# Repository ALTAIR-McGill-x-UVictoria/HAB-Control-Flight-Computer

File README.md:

# HAB-Control-Flight-Computer
High Altitude Balloon Flight Computer

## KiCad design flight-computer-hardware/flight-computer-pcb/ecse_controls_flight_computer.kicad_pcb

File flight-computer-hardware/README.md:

# Hardware Information

Flight computer PCB designed on KiCad, a free PCB design software.

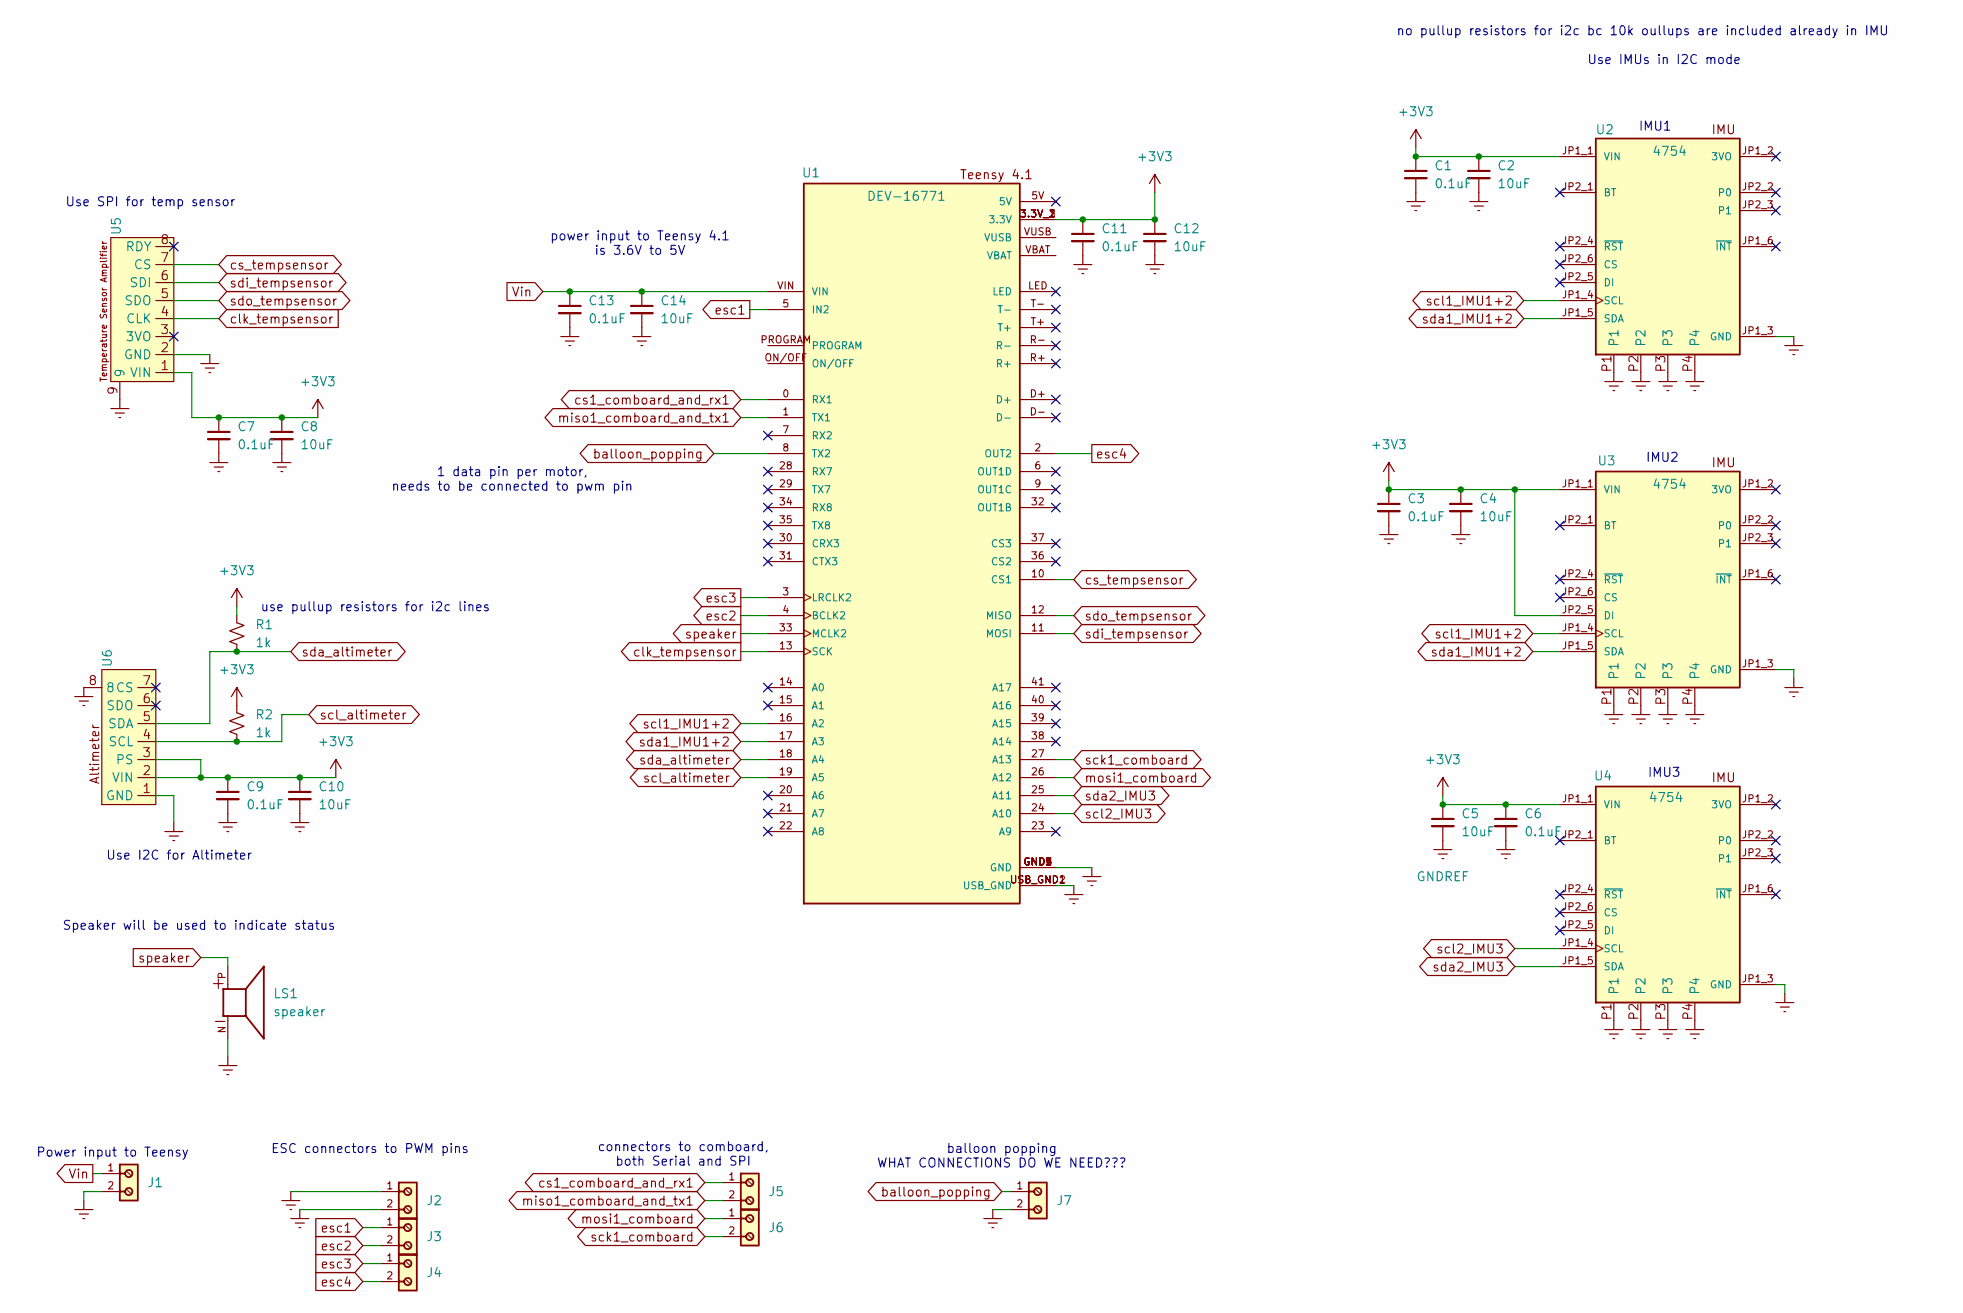
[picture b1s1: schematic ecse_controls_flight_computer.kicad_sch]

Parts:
C1, C3, C6, C7, C9, C11, C13: 0.1uF; C_0805_2012Metric_Pad1.18x1.45mm_HandSolder
C2, C4, C5, C8, C10, C12, C14: 10uF; C_0805_2012Metric_Pad1.18x1.45mm_HandSolder
J1, J2, J3, J4, J5, J6, J7: 691137710002; 691137710002-connector; PART-NUMBER 691137710002
LS1: speaker; PARTREV C
R1, R2: 1k; R_0805_2012Metric_Pad1.20x1.40mm_HandSolder
U1: DEV-16771; MODULE_DEV-16771; PARTREV 4.1
U2, U3, U4: 4754; MODULE_4754; PARTREV 2021-03-16
U5: temperature-amplifier
U6: altimeter

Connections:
+3V3: C1.1, C2.1, C3.1, C4.1, C5.1, C6.1, C7.1, C8.1, C9.1, C10.1, C11.1, C12.1, R1.1, R2.1, U1.3.3V_1 (3.3V), U1.3.3V_2 (3.3V), U1.3.3V_3 (3.3V), U2.JP1_1 (VIN), U3.JP1_1 (VIN), U3.JP2_5 (DI), U4.JP1_1 (VIN), U5.1 (VIN), U6.2 (VIN), U6.3 (PS)
GNDREF: C1.2, C2.2, C3.2, C4.2, C5.2, C6.2, C7.2, C8.2, C9.2, C10.2, C11.2, C12.2, C13.2, C14.2, J1.2, J2.1, J2.2, J7.2, LS1.N, U1.GND1 (GND), U1.GND2 (GND), U1.GND3 (GND), U1.GND4 (GND), U1.GND5 (GND), U1.USB_GND1 (USB_GND), U1.USB_GND2 (USB_GND), U2.JP1_3 (GND), U2.P1, U2.P2, U2.P3, U2.P4, U3.JP1_3 (GND), U3.P1, U3.P2, U3.P3, U3.P4, U4.JP1_3 (GND), U4.P1, U4.P2, U4.P3, U4.P4, U5.2 (GND), U5.9, U6.1 (GND), U6.8
Vin: C13.1, C14.1, J1.1, U1.VIN
balloon_popping: J7.1, U1.8 (TX2)
clk_tempsensor: U1.13 (SCK), U5.4 (CLK)
cs1_comboard_and_rx1: J5.1, U1.0 (RX1)
cs_tempsensor: U1.10 (CS1), U5.7 (CS)
esc1: J3.1, U1.5 (IN2)
esc2: J3.2, U1.4 (BCLK2)
esc3: J4.1, U1.3 (LRCLK2)
esc4: J4.2, U1.2 (OUT2)
miso1_comboard_and_tx1: J5.2, U1.1 (TX1)
mosi1_comboard: J6.1, U1.26 (A12)
sck1_comboard: J6.2, U1.27 (A13)
scl1_IMU1+2: U1.16 (A2), U2.JP1_4 (SCL), U3.JP1_4 (SCL)
scl2_IMU3: U1.24 (A10), U4.JP1_4 (SCL)
scl_altimeter: R2.2, U1.19 (A5), U6.4 (SCL)
sda1_IMU1+2: U1.17 (A3), U2.JP1_5 (SDA), U3.JP1_5 (SDA)
sda2_IMU3: U1.25 (A11), U4.JP1_5 (SDA)
sda_altimeter: R1.2, U1.18 (A4), U6.5 (SDA)
sdi_tempsensor: U1.11 (MOSI), U5.6 (SDI)
sdo_tempsensor: U1.12 (MISO), U5.5 (SDO)
speaker: LS1.P, U1.33 (MCLK2)

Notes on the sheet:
IMU3
use pullup resistors for i2c lines
IMU2
power input to Teensy 4.1 is 3.6V to 5V
Use I2C for Altimeter
connectors to comboard, both Serial and SPI
Use IMUs in I2C mode
balloon popping WHAT CONNECTIONS DO WE NEED???
Use SPI for temp sensor
no pullup resistors for i2c bc 10k oullups are included already in IMU
ESC connectors to PWM pins
1 data pin per motor, needs to be connected to pwm pin
Speaker will be used to indicate status
IMU1
Power input to Teensy

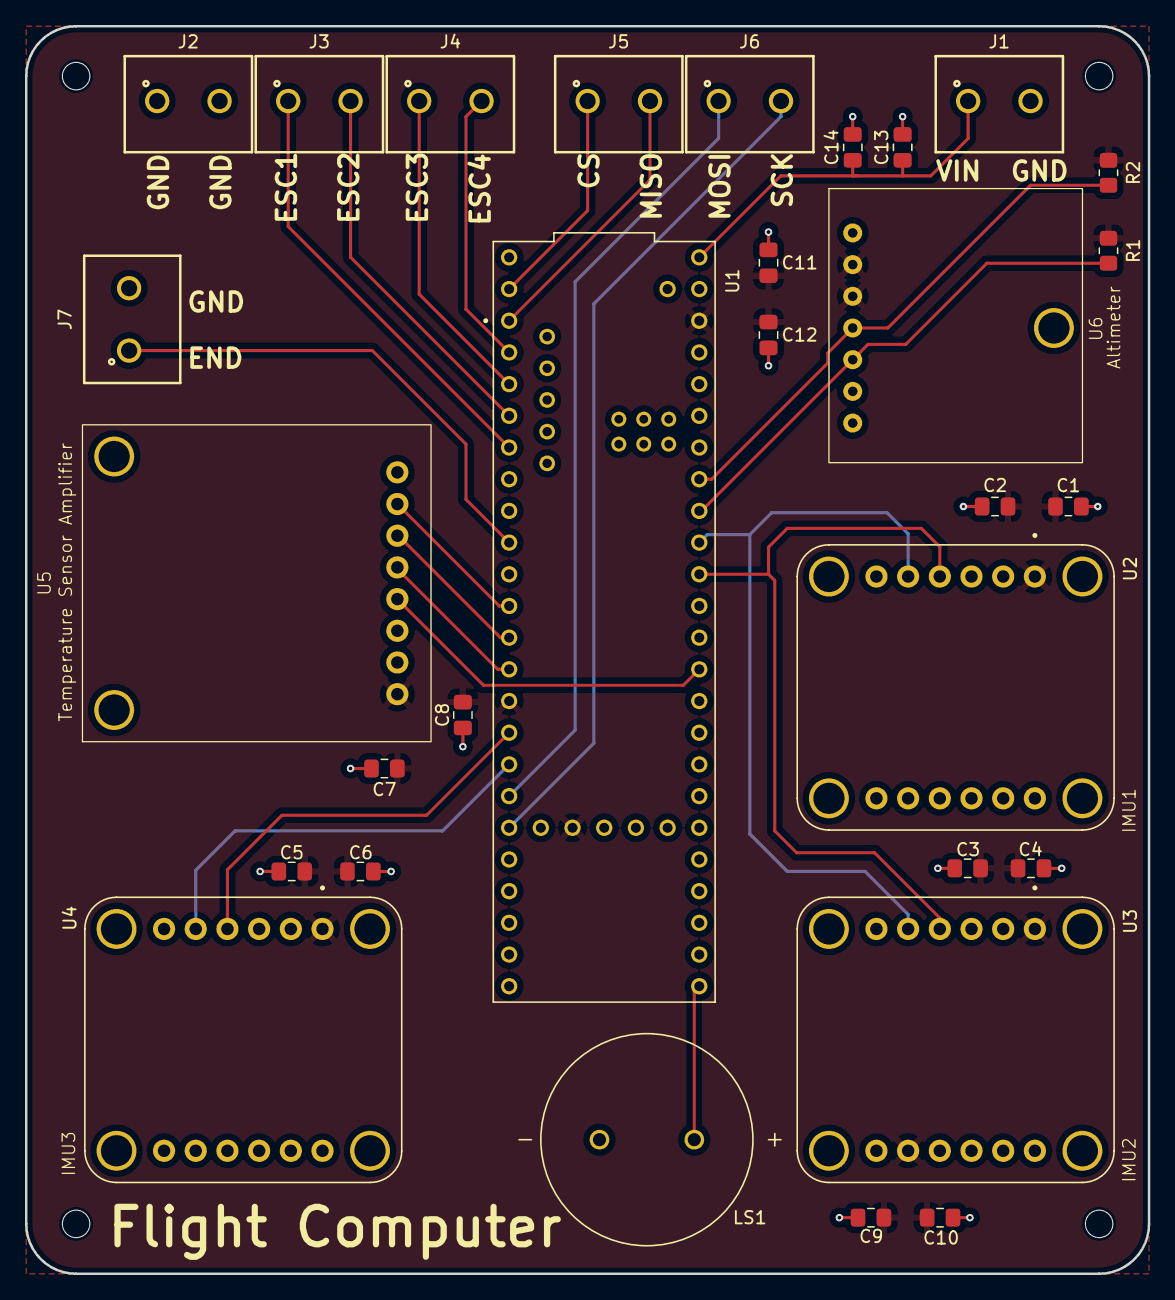
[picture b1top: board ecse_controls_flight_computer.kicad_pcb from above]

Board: 2 copper layers, 90.0 x 100.0 mm, 30 parts (0 on the bottom side), 23 nets.

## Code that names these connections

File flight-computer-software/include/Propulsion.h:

#ifndef PROPULSION_H
#define PROPULSION_H

#include <Arduino.h>
#include <Teensy_PWM.h>  // Include Teensy_PWM library
#include <TeensyThreads.h>

#define SPEAKER_PIN 33

class Propulsion {
public:
    // Constructor and destructor
    Propulsion(int esc1Pin = 4, int esc2Pin = 5)
        : ESC1_PIN(esc1Pin), ESC2_PIN(esc2Pin), esc1_pwm(nullptr), esc2_pwm(nullptr),
          leftThrottlePercent(0.0f), rightThrottlePercent(0.0f) {
        // Constructor initializes pin numbers, nulls the PWM pointers, and sets initial throttle to 0
    }
    
    ~Propulsion() {
        // Ensure resources are freed
        deinit();
    }
    
    // Main control methods
    bool init() {
        // Initialize Teensy_PWM objects with 0% duty cycle
        esc1_pwm = new Teensy_PWM(ESC1_PIN, ESC_FREQUENCY, 0.0f);
        esc2_pwm = new Teensy_PWM(ESC2_PIN, ESC_FREQUENCY, 0.0f);
        
        // Check if initialization was successful
        if (!esc1_pwm || !esc2_pwm || 
            !esc1_pwm->isPWMEnabled() || !esc2_pwm->isPWMEnabled()) {
            return false;
        }
        
        return true;
    }

    void calibrate(){
        // Set ESCs to maximum throttle for calibration
        esc1_pwm->setPWM(ESC1_PIN, ESC_FREQUENCY, MAX_DUTY_CYCLE);
        esc2_pwm->setPWM(ESC2_PIN, ESC_FREQUENCY, MAX_DUTY_CYCLE);
        // Beep to indicate to connect power to motors
        tone(SPEAKER_PIN, 700, 1000);
        threads.delay(1000);
        noTone(SPEAKER_PIN);
        
        delay(3000);  // Wait for 3 seconds

        
        // Beep to indicate to disconnect power from motors
        tone(SPEAKER_PIN, 700, 1000);
        threads.delay(1000);
        noTone(SPEAKER_PIN);
        
        delay(3000);  // Wait for 3 seconds
        // Set ESCs to minimum throttle for calibration
        esc1_pwm->setPWM(ESC1_PIN, ESC_FREQUENCY, MIN_DUTY_CYCLE);
        esc2_pwm->setPWM(ESC2_PIN, ESC_FREQUENCY, MIN_DUTY_CYCLE);
        
        delay(3000);  // Wait for 3 seconds
        // Beep to indicate to connect power to motors
        tone(SPEAKER_PIN, 700, 1000);
        threads.delay(1000);
        noTone(SPEAKER_PIN);

        delay(3000);  // Wait for 3 seconds
    }
    
    void deinit() {
        if (esc1_pwm) {
            delete esc1_pwm;
            esc1_pwm = nullptr;
        }
        if (esc2_pwm) {
            delete esc2_pwm;
            esc2_pwm = nullptr;
        }
    }
    
    void stopMotors() {
        if (esc1_pwm && esc2_pwm) {
            esc1_pwm->setPWM(ESC1_PIN, ESC_FREQUENCY, MIN_DUTY_CYCLE);
            esc2_pwm->setPWM(ESC2_PIN, ESC_FREQUENCY, MIN_DUTY_CYCLE);
            leftThrottlePercent = 0.0f;
            rightThrottlePercent = 0.0f;
        }
    }
    
    // Throttle control methods
    void setThrottle(float throttlePercent) {
        float dutyCycle = computeDutyCycle(throttlePercent);
        if (esc1_pwm && esc2_pwm) {
            esc1_pwm->setPWM(ESC1_PIN, ESC_FREQUENCY, dutyCycle);
            esc2_pwm->setPWM(ESC2_PIN, ESC_FREQUENCY, dutyCycle);
            leftThrottlePercent = throttlePercent;
            rightThrottlePercent = throttlePercent;
        }
    }
    
    void setLeftThrottle(float throttlePercent) {
        float dutyCycle = computeDutyCycle(throttlePercent);
        if (esc1_pwm) {
            esc1_pwm->setPWM(ESC1_PIN, ESC_FREQUENCY, dutyCycle);
            leftThrottlePercent = throttlePercent;
        }
    }
    
    void setRightThrottle(float throttlePercent) {
        float dutyCycle = computeDutyCycle(throttlePercent);
        if (esc2_pwm) {
            esc2_pwm->setPWM(ESC2_PIN, ESC_FREQUENCY, dutyCycle);
            rightThrottlePercent = throttlePercent;
        }
    }

    // Add these new getter methods
    float getLeftThrottle() const {
        return leftThrottlePercent;
    }
    
    float getRightThrottle() const {
        return rightThrottlePercent;
    }

private:
    // ESC pins
    const int ESC1_PIN;
    const int ESC2_PIN;
    
    // ESC frequency in Hz
    static const int ESC_FREQUENCY = 400;
    // ESC period in microseconds
    static constexpr float ESC_PERIOD = 1000000.0f / ESC_FREQUENCY;

    // ESC pulse width values in microseconds
    static const int MIN_PULSE_WIDTH = 1000;  // Zero throttle
    static const int MAX_PULSE_WIDTH = 2000;  // Full throttle
    
    // At 400Hz, period is 2500μs (1/400 = 0.0025s = 2500μs)
    // 1000/2500 = 40% duty cycle (zero throttle)
    // 2000/2500 = 80% duty cycle (full throttle)
    // Duty cycle values for ESC throttle percentage
    static constexpr float MIN_DUTY_CYCLE = (MIN_PULSE_WIDTH / ESC_PERIOD) * 100.0f;
    static constexpr float MAX_DUTY_CYCLE = (MAX_PULSE_WIDTH / ESC_PERIOD) * 100.0f;
    
    // PWM objects for the ESCs
    Teensy_PWM* esc1_pwm;
    Teensy_PWM* esc2_pwm;

    // Add these new private members to track throttle percentages
    float leftThrottlePercent;
    float rightThrottlePercent;

    // Helper function to map throttle percentage to duty cycle
    float computeDutyCycle(float throttlePercent) const {
        return (throttlePercent * (MAX_DUTY_CYCLE - MIN_DUTY_CYCLE) / 100.0f) + MIN_DUTY_CYCLE;
    }
};

#endif // PROPULSION_H

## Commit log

2025-02-12 added initial structure, sensor wrapper, and tests
2025-02-13 changed to project to PlatformIO from ArduinoIDE, updated project structure, added configs for test envs, and created readme for instructions
2025-02-15 Create Flight Computer PCB
2025-02-15 Rename Flight Computer PCB to Flight Computer PCB folder/Flight computer kicad
2025-02-15 added some code for sensor fusion (NOT TESTED YET)
2025-02-16 fixed hardware directory and added sensor fusion for IMUS (median filtering)
2025-02-16 implemented Weighted Average sensor fusion to compare with Median filtering
2025-02-23 detect if imu gets disconnected in sensorFusion function, commented code in header file
2025-02-23 editing some comments
2025-03-04 added angular velocity, made sensorfusion function private
2025-03-04 started state machine implementation
2025-03-04 not working yet
2025-03-04 creating first iteration of SPI communication protocol between ECSE power and ECSE control boards, testing pending
2025-03-04 added tests to platformio.ini file
2025-03-04 adam fixed file names
2025-03-04 fixed compilation issues
2025-03-04 deleted renamed test file for power board
2025-03-04 deleted renamed test file for control board
2025-03-04 added extra printing statements for confirmation
2025-03-04 testing status of SPI
2025-03-04 added more print statements
2025-03-04 state machine wip
2025-03-05 state machine another approach
2025-03-05 still not working yet, trying to get the angular velocity from the orientation (using functions getAngularVelocity and calculateAngularVelocity
2025-03-05 Added state machine framework
2025-03-05 added main base implementation using state machine
2025-03-06 Removed and cleaned main flight computer fsm
2025-03-06 Added cleaned transitions back
2025-03-06 Adjusted the number of transitions in fsm init
2025-03-06 updated sensors class to work for linear acceleration, angular velocity, and orientation simultaneously
2025-03-06 some fixes
2025-03-06 still debugging
2025-03-06 debugging
2025-03-06 debugging again
2025-03-06 identified issue and solved using threads
2025-03-07 fully working sensor class with threading
2025-03-07 cleanup
2025-03-07 added imu data invalidation after timeout to check for disconnection
2025-03-07 imu and alitmeter detect when disconnected
2025-03-07 updated report rate
2025-03-07 started filling in state machine
2025-03-07 added log queue
2025-03-08 made further adjustments to handshake protocol, ready for further testing
2025-03-08 made further changes, ready for a re-test
2025-03-08 added changes for re-test
2025-03-08 made further revisions for re-testing
2025-03-08 added delay to determine if timing is too short between SPI messages
2025-03-09 created simpler test to faciliate debugging for SPI
2025-03-09 updated comm control test code
2025-03-09 added delay to simple comm power test
2025-03-09 added end transaction
2025-03-09 added modified SPI library that supports slave mode and updated simple test code
2025-03-09 added SPI.begin() call for debugging purposes
2025-03-09 testing pin configuration
2025-03-09 removed unecessary line
2025-03-09 more debugging
2025-03-09 trying out test example using test pinout
2025-03-09 edited code to test serial connection instead of SPI using sample test code
2025-03-09 updated serial ports
2025-03-09 more testing with the same interface
2025-03-09 modified base code that established communication to send some dummy data to determine if it is indeed being processed properly
2025-03-09 added debugging statements
2025-03-09 updated code to have packet header reading before reading remainder of message
2025-03-10 serial into class with alex
2025-03-10 cleaned up
2025-03-10 simplified
2025-03-10 testing
2025-03-10 testing again
2025-03-10 working
2025-03-10 formatting
2025-03-10 deleted old communication testing directories
2025-03-10 deleted previous directory for spi control board
2025-03-10 deleted previous header for SPI communication (no longer in use)
2025-03-10 deleted previous SPI library (no longer in use)
2025-03-10 renamed files
2025-03-10 updated baud rate
2025-03-11 added check for imu i2c begin
2025-03-12 updated communication test files
2025-03-12 updated verifyCommunication() function
2025-03-12 communication verification working and cleanup
2025-03-12 updated data_collection_thread() and adding placeholder logging messages for SD card
2025-03-17 updated log queue to be more flexible and added SD card logging to log queue test
2025-03-17 updated main for improved log queue implementation
2025-03-18 improved sensor class with status checking and restart logic
2025-03-18 fixed sensor status tracking to only restart altimeter if it fails since the IMUs cannot work this way after some testing
2025-03-18 cleaned up sensors code
2025-03-19 sensors code improvements
2025-03-19 entire team MEGA group coding session
2025-03-19 updated log queue test
2025-03-20 corrected some errors in the main file
2025-03-22 updated comments in SerialCommunication.h
2025-03-30 team coding session, completed main except for stabilization and motor control
2025-03-31 added world frame conversions to sensors class
2025-03-31 added propulsion class and test file
2025-04-03 cleaned up and improved propulsion code based on the testing
2025-04-06 Added testing code for the RL agent
2025-04-07 Added propulsion to the RL agent test
2025-04-07 Added new weights for the RL agent
2025-04-07 Testing model and propulsion with logs
2025-04-11 Added log file for model test
2025-05-16 reducing memory usage
2025-05-16 compiles and runs in concurrency
2025-05-20 working inference but imu angle bug
2025-05-20 test imu setup
2025-05-21 diagnosing IMU issues
2025-05-21 confirmed single IMU working with calibration, reorganizing code
2025-05-22 more robust imu handling, adding gps integration, kalman filtering start
2025-05-22 working on sensor data filtering,
    need better accuracy on world velocity and position. changing thread priority puts program in deadlock. try to optimize average IMU sensor dt
2025-05-22 state machine poll one IMU per thread loop
    issues: orientation and accelerometer values incredibly slow to update
2026-02-13 push
